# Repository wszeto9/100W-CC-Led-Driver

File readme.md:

# 100W RGB LED Constant Current Driver
A constant current driver made to to drive 100W RGB COB LEDs

[Interactive BOM](https://htmlpreview.github.io/?https://raw.githubusercontent.com/wszeto9/100W-CC-Led-Driver/main/Documentation/ibom.html)

<h2> Features:</h2>
<ul>

<li>3 Constant current outputs for Red, Green, and Blue channel</li>
<li>Controlled with an ESP8266 running WLED and connected over Wi-Fi</li>
<li>Panelized in a 2x2 panel of 100x100mm for minimal fabrication costs at JLCPCB</li>
<li>BOM cost is kept low at around $6 per board
</ul>
<h2>Pinout</h2>

<h2> Bring-up and Usage </h2>

- Follow the iBOM and solder all items onto the board. 
- Attach the programming device onto the mezzamine connector on the top left of the board
- Program the ESP8266 with WLED
- Setup WLED with a single analog RGB channel attached to it. The pinouts should be:
    - Green: GPIO 13
    - Red: GPIO 12
    - Blue: GPIO 14
- Unplug the programming header and attach the LED and a 24V/5A power supply to the screw terminals
- Connect to the ESP's Wi-Fi network and turn on the lights!

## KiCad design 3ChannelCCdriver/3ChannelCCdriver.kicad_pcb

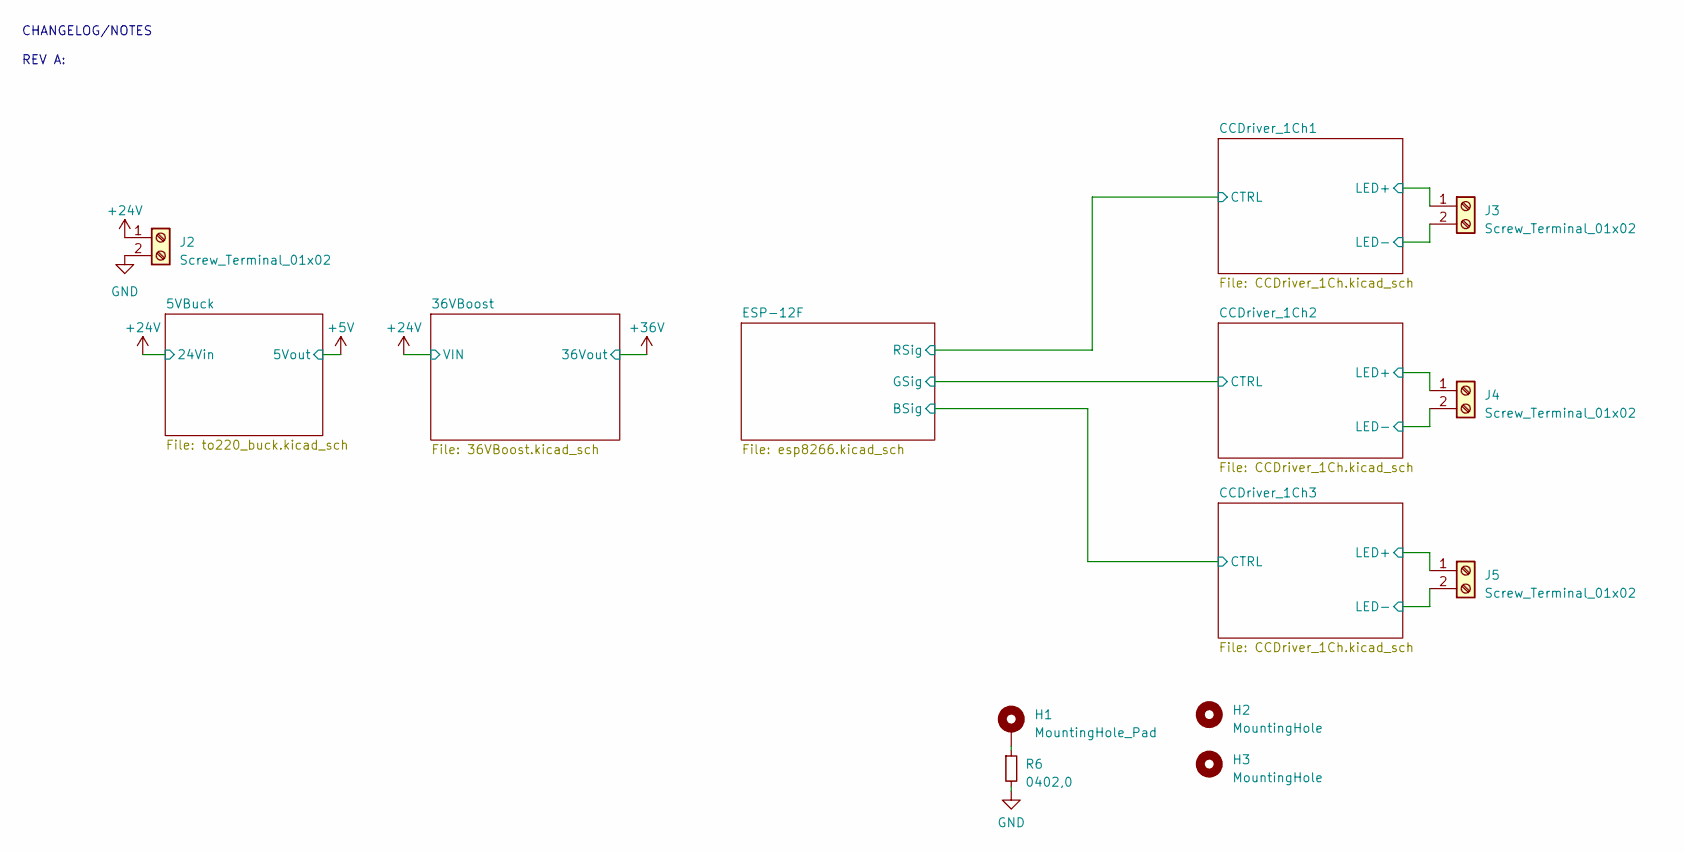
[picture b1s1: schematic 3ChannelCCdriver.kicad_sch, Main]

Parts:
H1: MountingHole_Pad; MountingHole_3.2mm_M3_DIN965_Pad
H2, H3: MountingHole; MountingHole_3.2mm_M3
J2: Screw_Terminal_01x02; TerminalBlock_Phoenix_MKDS-1,5-2-5.08_1x02_P5.08mm_Horizont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
J3, J4, J5: Screw_Terminal_01x02; TerminalBlock_TE_282834-2_1x02_P2.54mm_Horizontal; LCSC C2922597
R6: 0402,0; R_0402_1005Metric; MFGPN 0402WGF0000TCE; LCSC C17168

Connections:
+24V: J2.1; also elsewhere on the board
/CCDriver_1Ch1/LED+: J3.1; also elsewhere on the board
/CCDriver_1Ch1/LED-: J3.2; also elsewhere on the board
/CCDriver_1Ch2/LED+: J4.1; also elsewhere on the board
/CCDriver_1Ch2/LED-: J4.2; also elsewhere on the board
/CCDriver_1Ch3/LED+: J5.1; also elsewhere on the board
/CCDriver_1Ch3/LED-: J5.2; also elsewhere on the board
GND: J2.2, R6.2; also elsewhere on the board
unnamed: H1.1, R6.1

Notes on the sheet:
CHANGELOG/NOTES REV A:

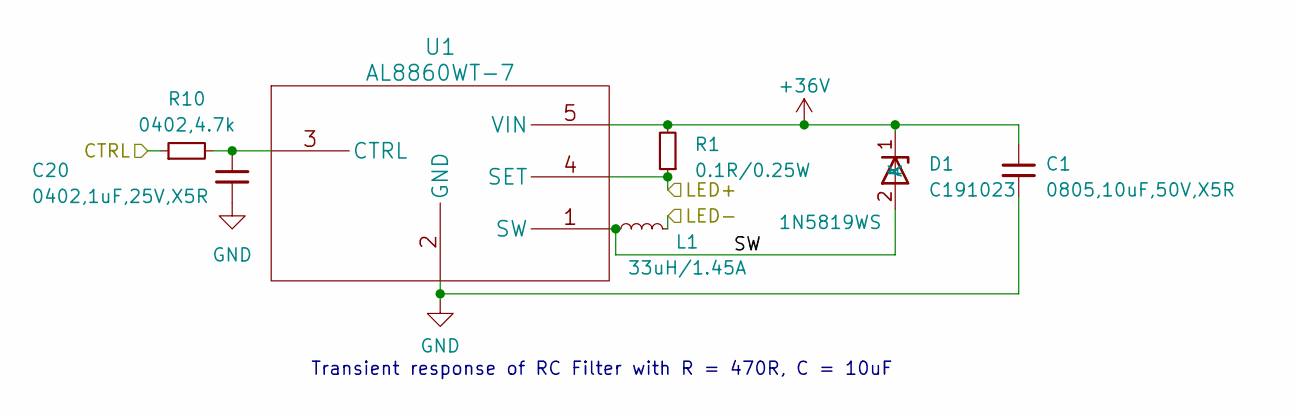
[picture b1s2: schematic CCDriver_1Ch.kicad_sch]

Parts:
C1: 0805,10uF,50V,X5R; C_0805_2012Metric; MFGPN GRM21BR61H106KE43L; LCSC C440198
C20: 0402,1uF,25V,X5R; C_0402_1005Metric; MFGPN CL05A105KA5NQNC; LCSC C52923
D1: 1N5819WS; D_SOD-323; LCSC C191023
L1: 33uH/1.45A; L_Bourns-SRN6028; LCSC C354635
R1: 0.1R/0.25W; R_0805_2012Metric; LCSC C171367
R10: 0402,4.7k; R_0402_1005Metric; MFGPN 0402WGF4701TCE; LCSC C25900
U1: AL8860WT-7; TSOT-23-5; LCSC C125330

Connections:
+36V: C1.1, D1.1 (K), R1.2, U1.5 (VIN); also elsewhere on the board
/CCDriver_1Ch1/CTRL: R10.1; also elsewhere on the board
/CCDriver_1Ch3/LED+: R1.1, U1.4 (SET); also elsewhere on the board
/CCDriver_1Ch3/LED-: L1.2; also elsewhere on the board
/CCDriver_1Ch3/SW: D1.2 (A), L1.1, U1.1 (SW)
GND: C1.2, C20.2, U1.2 (GND); also elsewhere on the board

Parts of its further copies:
C2, C3: 0805,10uF,50V,X5R; C_0805_2012Metric; MFGPN GRM21BR61H106KE43L; LCSC C440198
C19, C21: 0402,1uF,25V,X5R; C_0402_1005Metric; MFGPN CL05A105KA5NQNC; LCSC C52923
D2, D3: 1N5819WS; D_SOD-323; LCSC C191023
L2, L3: 33uH/1.45A; L_Bourns-SRN6028; LCSC C354635
R2, R3: 0.1R/0.25W; R_0805_2012Metric; LCSC C171367
R7, R11: 0402,4.7k; R_0402_1005Metric; MFGPN 0402WGF4701TCE; LCSC C25900
U2, U3: AL8860WT-7; TSOT-23-5; LCSC C125330

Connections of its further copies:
+36V: C2.1, C3.1, D2.1 (K), D3.1 (K), R2.2, R3.2, U2.5 (VIN), U3.5 (VIN); also elsewhere on the board
/CCDriver_1Ch1/LED+: R2.1, U2.4 (SET); also elsewhere on the board
/CCDriver_1Ch1/LED-: L2.2; also elsewhere on the board
/CCDriver_1Ch1/SW: D2.2 (A), L2.1, U2.1 (SW)
/CCDriver_1Ch2/CTRL: R11.1; also elsewhere on the board
/CCDriver_1Ch2/LED+: R3.1, U3.4 (SET); also elsewhere on the board
/CCDriver_1Ch2/LED-: L3.2; also elsewhere on the board
/CCDriver_1Ch2/SW: D3.2 (A), L3.1, U3.1 (SW)
/CCDriver_1Ch3/CTRL: R7.1; also elsewhere on the board
GND: C2.2, C3.2, C19.2, C21.2, U2.2 (GND), U3.2 (GND); also elsewhere on the board
unnamed: C21.1, R11.2, U3.3 (CTRL)

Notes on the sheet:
Transient response of RC Filter with R = 470R, C = 10uF

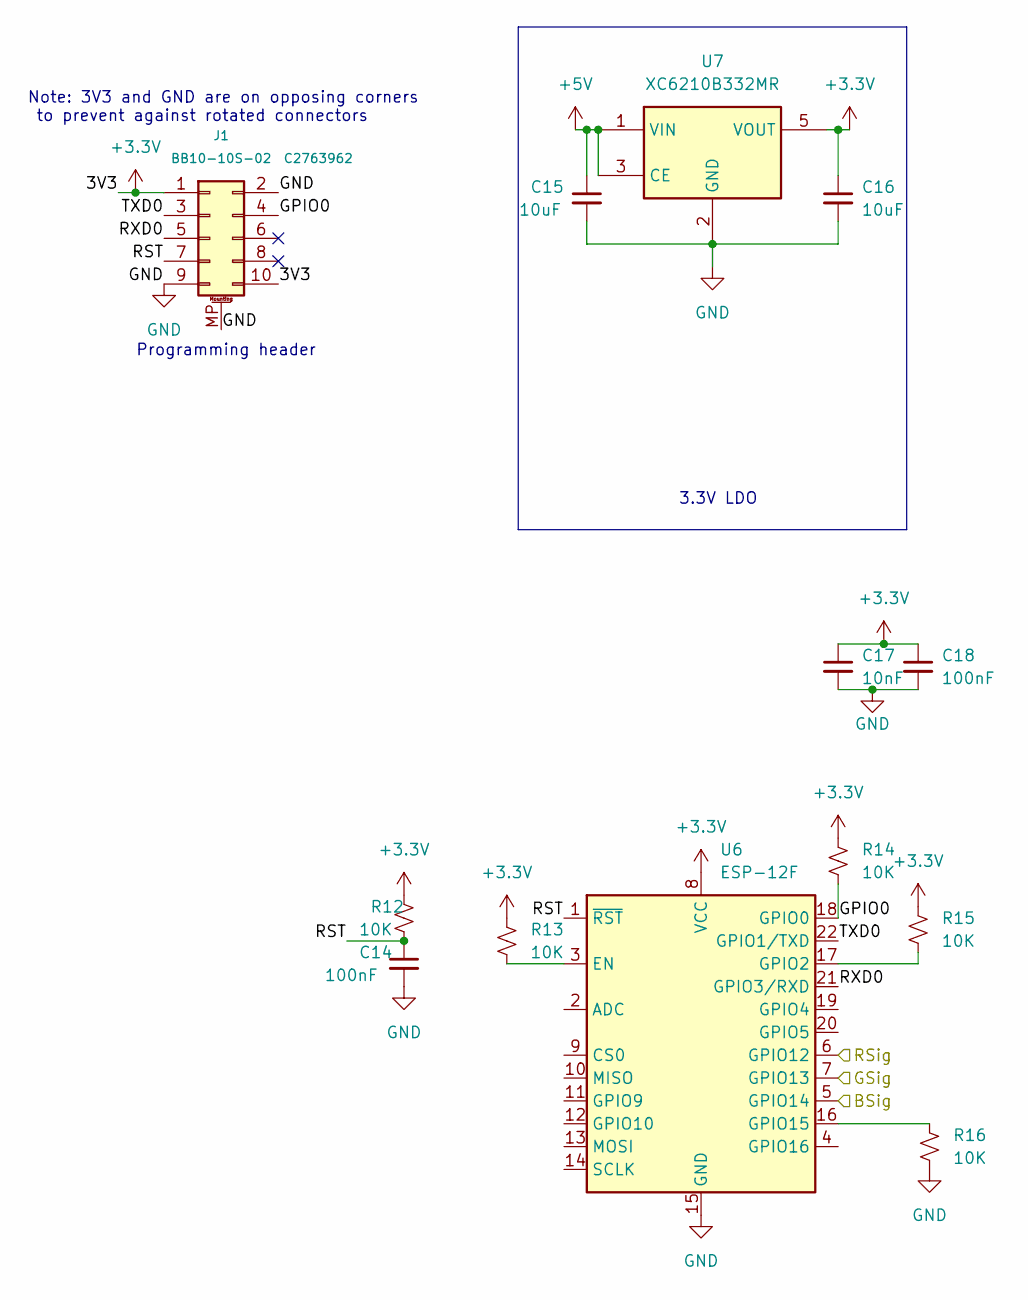
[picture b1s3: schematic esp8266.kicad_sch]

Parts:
C14, C18: 100nF; C_0402_1005Metric; LCSC Part Number C1525
C15, C16: 10uF; C_0402_1005Metric; LCSC Part Number C15525
C17: 10nF; C_0402_1005Metric; LCSC Part Number C15195
J1: BB10-10S-02; YXT-BB10-10S-02; LCSC C2763962
R12, R13, R14, R15, R16: 10K; R_0402_1005Metric; LCSC Part Number C25744
U6: ESP-12F; ESP-12E
U7: XC6210B332MR; SOT-23-5; LCSC Part Number C424705

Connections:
+3.3V: C16.1, C17.1, C18.1, J1.1, J1.10, R12.2, R13.2, R14.1, R15.1, U6.8 (VCC), U7.5 (VOUT)
+5V: C15.1, U7.1 (VIN), U7.3 (CE); also elsewhere on the board
/CCDriver_1Ch1/CTRL: U6.6 (GPIO12); also elsewhere on the board
/CCDriver_1Ch2/CTRL: U6.7 (GPIO13); also elsewhere on the board
/CCDriver_1Ch3/CTRL: U6.5 (GPIO14); also elsewhere on the board
/ESP-12F/GPIO0: J1.4, R14.2, U6.18 (GPIO0)
/ESP-12F/RST: C14.1, J1.7, R12.1, U6.1 (~RST)
/ESP-12F/RXD0: J1.5, U6.21 (GPIO3/RXD)
/ESP-12F/TXD0: J1.3, U6.22 (GPIO1/TXD)
GND: C14.2, C15.2, C16.2, C17.2, C18.2, J1.2, J1.9, J1.MP (MountPin), R16.2, U6.15 (GND), U7.2 (GND); also elsewhere on the board
unnamed: R13.1, U6.3 (EN)
unnamed: R15.2, U6.17 (GPIO2)
unnamed: R16.1, U6.16 (GPIO15)

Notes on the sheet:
Programming header
3.3V LDO
Note: 3V3 and GND are on opposing corners to prevent against rotated connectors

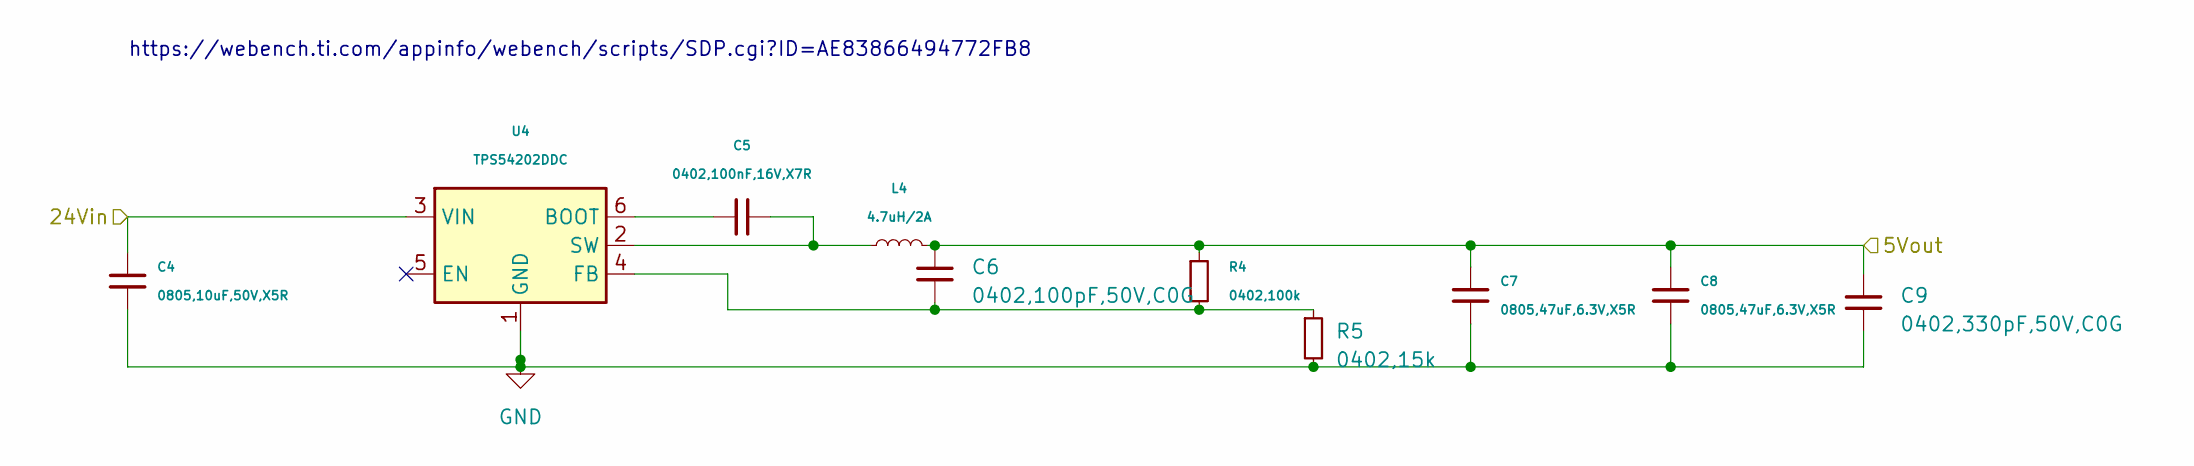
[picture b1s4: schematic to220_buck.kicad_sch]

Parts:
C4: 0805,10uF,50V,X5R; C_0805_2012Metric; MFGPN GRM21BR61H106KE43L; LCSC C440198
C5: 0402,100nF,16V,X7R; C_0402_1005Metric; MFGPN CL05B104KO5NNNC; LCSC C1525
C6: 0402,100pF,50V,C0G; C_0402_1005Metric; MFGPN 0402CG101J500NT; LCSC C1546
C7, C8: 0805,47uF,6.3V,X5R; C_0805_2012Metric; MFGPN CL21A476MQYNNNE; LCSC C16780
C9: 0402,330pF,50V,C0G; C_0402_1005Metric; MFGPN CL05C331JB5NNNC; LCSC C13533
L4: 4.7uH/2A; L_Wuerth_MAPI-4030; MFGPN YNR4030-4R7M; LCSC C340391
R4: 0402,100k; R_0402_1005Metric; MFGPN 0402WGF1003TCE; LCSC C25741
R5: 0402,15k; R_0402_1005Metric; MFGPN 0402WGF1502TCE; LCSC C25756
U4: TPS54202DDC; SOT-23-6; MFGPN TPS54202DDCR; LCSC C191884

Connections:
+5V: C6.1, C7.1, C8.1, C9.1, L4.2, R4.1; also elsewhere on the board
+24V: C4.1, U4.3 (VIN); also elsewhere on the board
GND: C4.2, C7.2, C8.2, C9.2, R5.2, U4.1 (GND); also elsewhere on the board
unnamed: C5.1, U4.6 (BOOT)
unnamed: C6.2, R4.2, R5.1, U4.4 (FB)
unnamed: C5.2, L4.1, U4.2 (SW)

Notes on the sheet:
https://webench.ti.com/appinfo/webench/scripts/SDP.cgi?ID=AE83866494772FB8

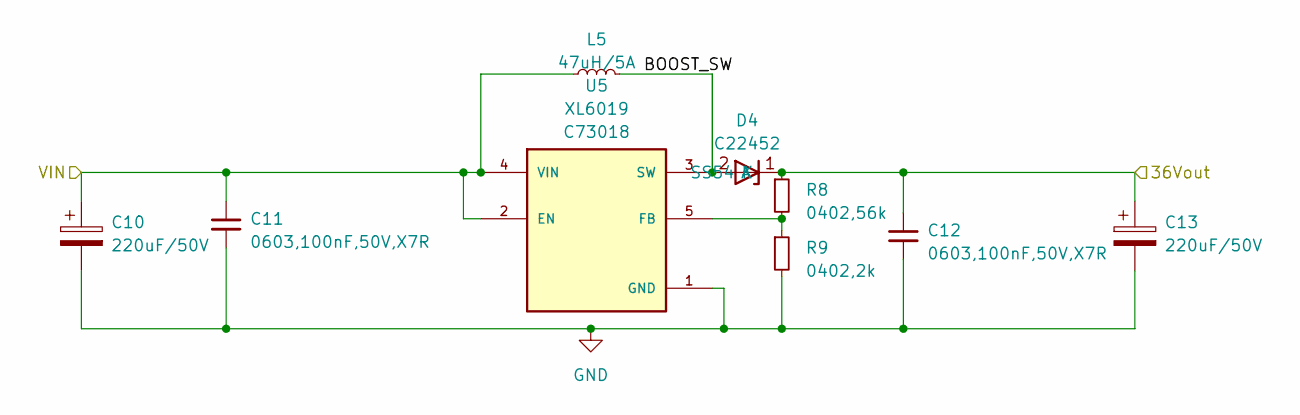
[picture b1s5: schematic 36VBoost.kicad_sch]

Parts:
C10, C13: 220uF/50V; CP_Radial_D8.0mm_P3.50mm; LCSC C2836445
C11, C12: 0603,100nF,50V,X7R; C_0603_1608Metric; MFGPN CC0603KRX7R9BB104; LCSC C2886384
D4: SS54; D_SMA; LCSC C22452
L5: 47uH/5A; L_Bourns_SRP1245A; LCSC C497913
R8: 0402,56k; R_0402_1005Metric; MFGPN 0402WGF5602TCE; LCSC C25796
R9: 0402,2k; R_0402_1005Metric; MFGPN 0402WGF2001TCE; LCSC C4109
U5: XL6019; TO-263-5_TabPin3; PARTREV 1.1; LCSC C73018

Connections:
+24V: C10.1, C11.1, L5.1, U5.2 (EN), U5.4 (VIN); also elsewhere on the board
+36V: C12.1, C13.1, D4.1 (K), R8.1; also elsewhere on the board
/36VBoost/BOOST_SW: D4.2 (A), L5.2, U5.3 (SW)
GND: C10.2, C11.2, C12.2, C13.2, R9.2, U5.1 (GND); also elsewhere on the board
unnamed: R8.2, R9.1, U5.5 (FB)

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
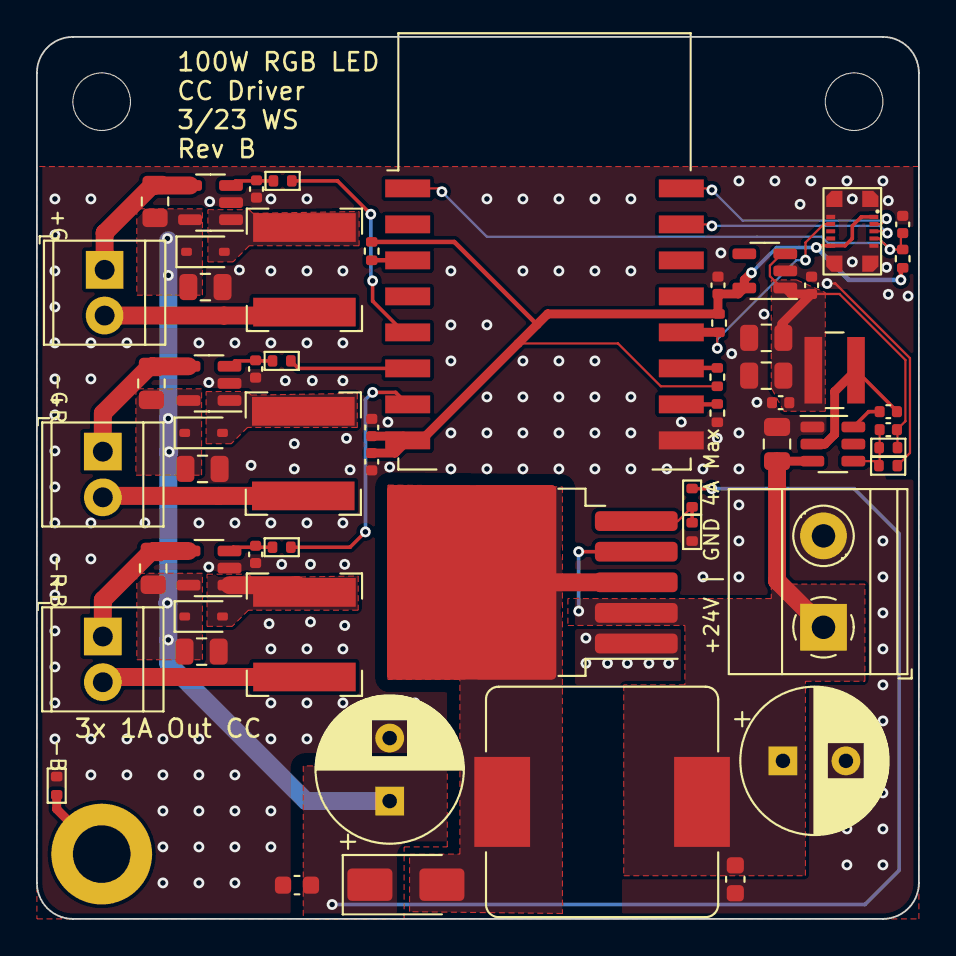
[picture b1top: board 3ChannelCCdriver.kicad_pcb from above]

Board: 2 copper layers, 49.0 x 49.0 mm, 61 parts (0 on the bottom side), 33 nets.

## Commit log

2023-03-07 laid out board
2023-03-14 Added documentation
2023-03-14 Moved documentation
2023-03-14 moved ibom
2023-04-03 Changed rev to B01
    Changed diode pinout on CC driver
2023-04-11 changed panelization
2023-12-02 neat-ified schematics
